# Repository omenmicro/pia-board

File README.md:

#OMEN PIA

Two 8bit serial port, designed for the [OMEN Computers](//github.com/osmibity/) with the system bus (Alpha, Bravo, Kilo, ...)

It uses the Motorola 68B21 PIA chip, or its 65xx equivalent 6521 (available from the WDC as [W65C21](http://westerndesigncenter.com/wdc/w65c21-chip.cfm)).

Board allows some options:

- Power supply
  - Direct supply for 5 V
  - Voltage regulator for supply 7 - 12 V
- RESET invertor (OMEN Alpha has positive RESET, others have inverted /RESET)
- IO selector (you can select IO1 to IO7 using simple switch)

## Parts

- Motorola MC68B21 or equivalent (W65C21, R6521 etc)
- IO socket DIL, 40 pin, wide
- Pin headers for the OMEN Bus, IO switch, port data pins
- Switches for LDO and RESET polarity
- (Optionally) 7805 LDO voltage regulator + 2x capacitor 10M
- (Optionally) SMD invertor 74AHC1G04D for reverting the RESET polarity

## Usage

Select the right IOx address space. For addresses value of each IOx, consult your OMEN manual.

See [datasheet](docs/datasheet) to further detail about programming.

## Ports

Ports are connected to 2x5 pin header each. 

Each header has 8 data pin, Vcc and GND.

Special header JP8 has connected the CA1, CA2, CB1 and CB2 control pins.

### RESET circuit

For Kilo, Bravo etc. with inverted RESET, just connect RES pin "+" (1-2)
For Alpha: Solder the invertor 74AHC1G04D and connect RES pin "-" (2-3)
Alpha hack: just solder a wire between the middle pin of RES switch and VCC (e.g. pin 20 of PIA IC)

### Power circuit

If you have the regulated voltage supply 5V, you can connect it directly here. Please use two switches (JP3, JP4), both on "VIN" position. *CAUTION! Supply input is connected directly to the system Vcc, so leave the supply input on the CPU board not connected!*

You can use the place for the 7805 regulator (up to 2 A). Solder the regulator and tvo capacitors, and select option "LDO" on both switches JP3, JP4. Connect power supply 7 - 12 V. Use heat sink for the regulator!

If you does not use the dedicated power supply, just leave both switches open and omit the power supply connector, voltage regulator as well as both capacitors.

## System bus pinout

| Pin | Signal
| --- | ---
| 1  | /WR
| 2  | D0
| 3  | D1
| 4  | D2
| 5  | D3
| 6  | D4
| 7  | D5
| 8  | D6
| 9  | D7
| 10 |  A0
| 11 |  A1
| 12 |  A2 (not connected in OMEN PIA)
| 13 |  /RD
| 14 |  IO1 (active low)
| 15 |  IO2
| 16 |  IO3
| 17 |  IO4
| 18 |  IO5
| 19 |  IO6
| 20 |  IO7
| 21 |  Vcc
| 22 |  GND
| 23 |  IRQ (not connected in OMEN PIA)
| 24 |  Clock
| 25 |  /RESET
| 26 |  /WAIT (not connected in OMEN PIA)
| 27 |  /BUSRQ (not connected in OMEN PIA)
| 28 |  /BUSACK (not connected in OMEN PIA)
| 29 |  (Reserved for future use)
| 30 |  (Reserved for future use)

### License

[CERN OHL](LICENSE.txt)

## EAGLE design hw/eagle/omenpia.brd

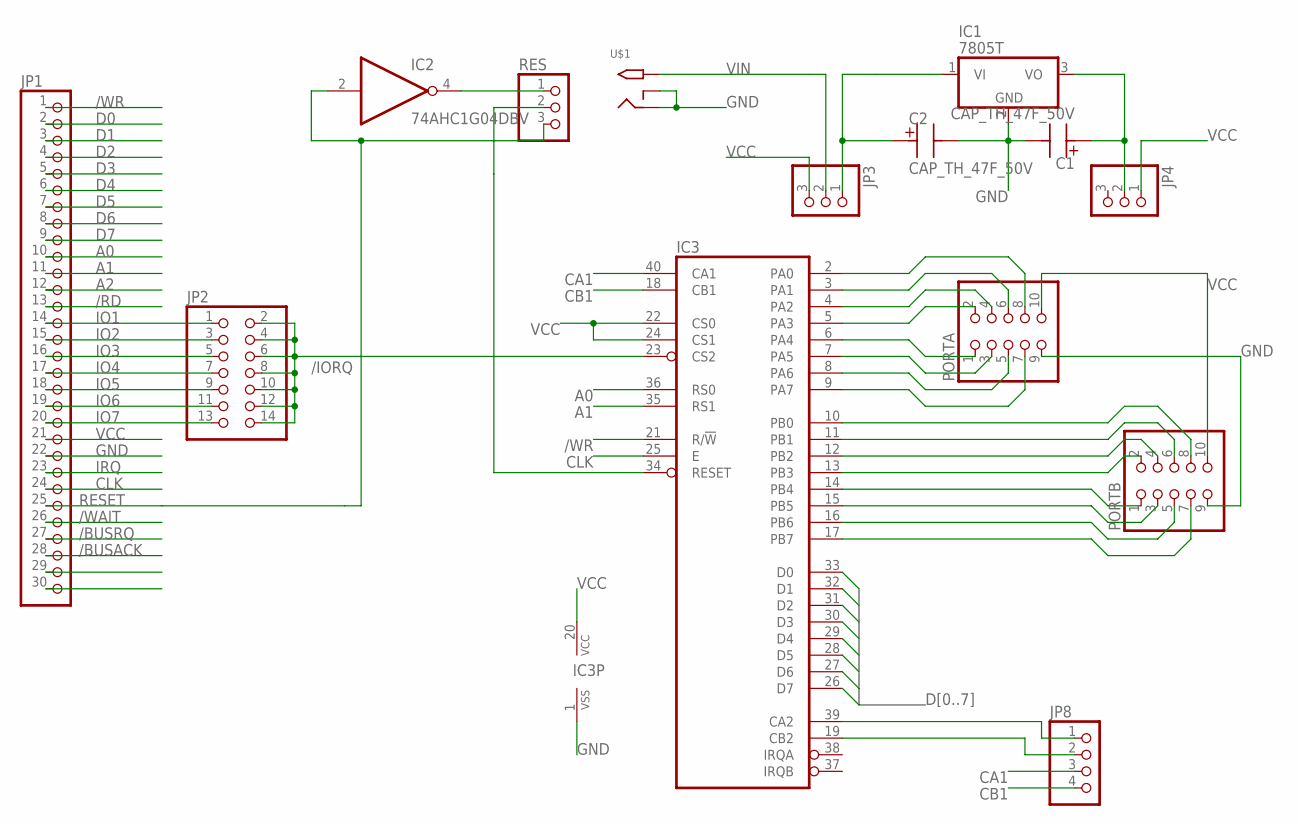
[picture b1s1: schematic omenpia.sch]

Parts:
C1, C2: CAP_TH_47F_50V; CAP_TH_P25_D63_POL
IC1: 7805T; TO220H
IC2: 74AHC1G04DBV; SOT23-5
IC3: 6821; DIL40
JP1: PINHD-1X30; 1X30
JP2: PINHD-2X7; 2X07
JP3, JP4: PINHD-1X3; 1X03
JP8: PINHD-1X4; 1X04
PORTA: PINHD-2X5; 2X05
PORTB: PINHD-2X5; 2X05
RES: PINHD-1X3; 1X03
U$1: 2.1MMJACKTHM; PJ-102A

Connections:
/BUSACK: JP1.28
/BUSRQ: JP1.27
/IORQ: IC3.23 (CS2), JP2.2, JP2.4, JP2.6, JP2.8, JP2.10, JP2.12, JP2.14
/RD: JP1.13
/WAIT: JP1.26
/WR: IC3.21 (R/!W), JP1.1
A0: IC3.36 (RS0), JP1.10
A1: IC3.35 (RS1), JP1.11
A2: JP1.12
CA1: IC3.40 (CA1), JP8.3
CB1: IC3.18 (CB1), JP8.4
CLK: IC3.25 (E), JP1.24
D0: IC3.33 (D0), JP1.2
D1: IC3.32 (D1), JP1.3
D2: IC3.31 (D2), JP1.4
D3: IC3.30 (D3), JP1.5
D4: IC3.29 (D4), JP1.6
D5: IC3.28 (D5), JP1.7
D6: IC3.27 (D6), JP1.8
D7: IC3.26 (D7), JP1.9
GND: C1.P$M, C2.P$M, IC1.2 (GND), IC2.3 (GND), IC3.1 (VSS), JP1.22, PORTA.9, PORTB.9, U$1.RING, U$1.RING_SW
IO1: JP1.14, JP2.1
IO2: JP1.15, JP2.3
IO3: JP1.16, JP2.5
IO4: JP1.17, JP2.7
IO5: JP1.18, JP2.9
IO6: JP1.19, JP2.11
IO7: JP1.20, JP2.13
IRQ: JP1.23
unnamed: IC3.5 (PA3), PORTA.2
unnamed: C2.P$P, IC1.1 (VI), JP3.1
unnamed: C1.P$P, IC1.3 (VO), JP4.2
unnamed: IC2.4 (O), RES.1
unnamed: IC3.4 (PA2), PORTA.4
unnamed: IC3.34 (RESET), RES.2
unnamed: IC3.3 (PA1), PORTA.6
unnamed: IC3.2 (PA0), PORTA.8
unnamed: IC3.6 (PA4), PORTA.1
unnamed: IC3.7 (PA5), PORTA.3
unnamed: IC3.8 (PA6), PORTA.5
unnamed: IC3.9 (PA7), PORTA.7
unnamed: IC3.10 (PB0), PORTB.8
unnamed: IC3.13 (PB3), PORTB.2
unnamed: IC3.12 (PB2), PORTB.4
unnamed: IC3.11 (PB1), PORTB.6
unnamed: IC3.14 (PB4), PORTB.1
unnamed: IC3.15 (PB5), PORTB.3
unnamed: IC3.16 (PB6), PORTB.5
unnamed: IC3.17 (PB7), PORTB.7
unnamed: IC3.39 (CA2), JP8.1
unnamed: IC3.19 (CB2), JP8.2
RESET: IC2.2 (I), JP1.25, RES.3
VCC: IC2.5 (VCC), IC3.20 (VCC), IC3.22 (CS0), IC3.24 (CS1), JP1.21, JP3.3, JP4.1, PORTA.10, PORTB.10
VIN: JP3.2, U$1.TIP

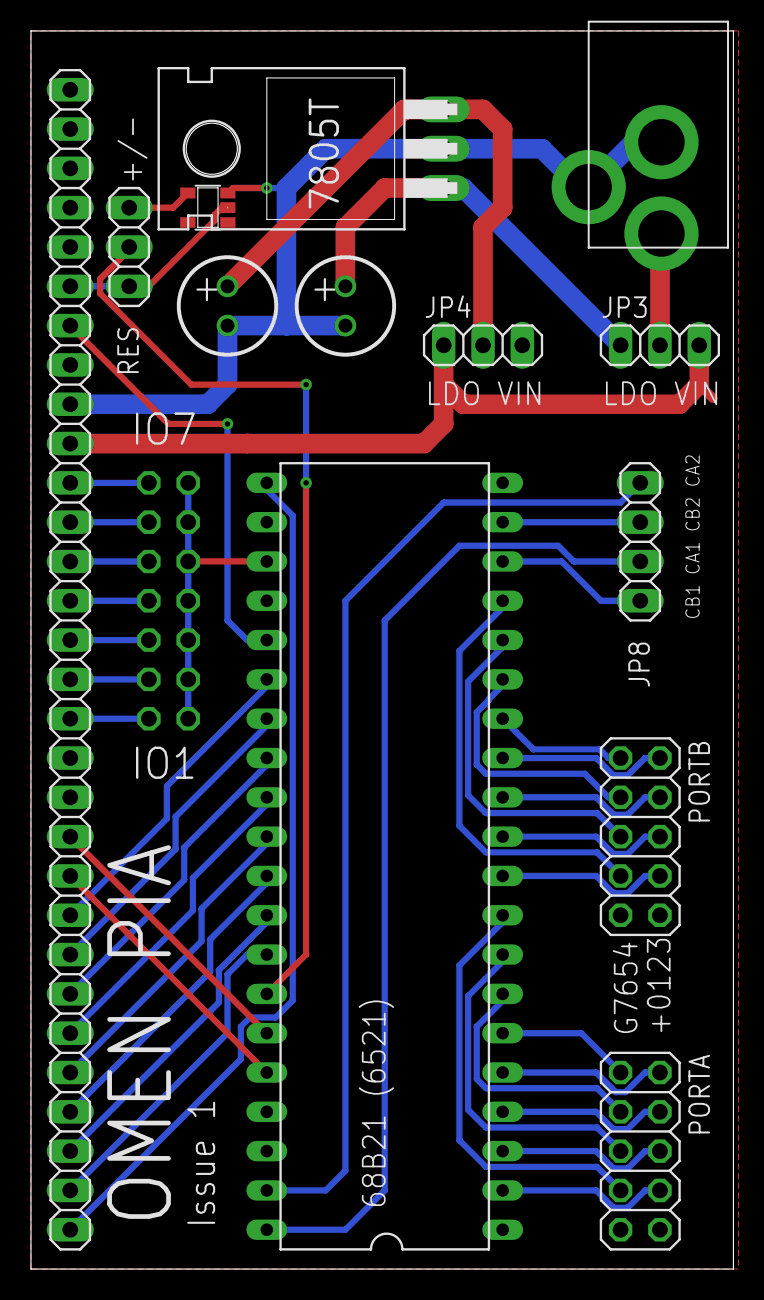
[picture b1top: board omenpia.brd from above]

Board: 2 copper layers, 45.4 x 80.0 mm, 14 parts (1 on the bottom side), 48 nets.

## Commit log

2018-11-24 Inti
2018-11-24 Readme
2018-11-24 board
2018-11-24 License
2018-11-24 Bus pinout
2018-11-24 table
2018-11-24 Test program
2018-12-16 Manual
